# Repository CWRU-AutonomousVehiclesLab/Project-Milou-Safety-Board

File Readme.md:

# Project Milou Safety Board
This repo contains Project Milou's safety board design. The goal of this design is to have a standardized modular designed board that allow other competitor to improve their safety system.

## What is Project Milou?
Project Milou is Case Western Reserve University's second autonomous snowplow robot. The robot actively participate in the ION Autonomous Snowplow Challenge. Currently the latest revision of the robot is utilizing a Teensy 3.6, an ITX computer with a core i5 as its main control system.

## Logistics

**Latest revision is done at Febuary, 2020.**

The designer of this board can be traced back maybe 5 years, designed by folks working with Project Otto. This board re-layed out by Ziyi Huang as part of fullfilment for his senior project fall 2019. The board is modified by Frank (Chude Qian) to make it work on the robot. 

This project is maintained under CWRU Auontomous Vehicles Lab till 2021, and further maintained under CWRU Biologically Inspired Robotics (Biorobotics) Center. 

*Copyright belongs to CWRU Autonomous Vehicles lab, CWRU Biologically Inspired Robotics (Biorobotic) Center. Please use with acknowledgement.*

### Contact for questions
To contact email [Frank](mailto:cxq41@case.edu) if it is before 2021. If it is after 2021, email [Ian](mailto:ija2@case.edu) and [Dr. Merat](mailto:flm@case.edu). 

## How to use this?
To use the safety board design, you do not necessarily need to know about making PCBS. We recommend you to have some basic understanding of Egale the PCB software if you want to modify it. It should be fairly easy to use on a standardized ROS enabled robot.

### Pressumptions
The board assumes the following components: a 5V supply, a 12V supply, a standard RC Spread Specturum 2.4G remote reciever, a digital microcontroller that is capable of 5V or 3.3V digital input and output, a standard E-stop Button and a 12V relay.

### Materials
In order to use this PCB board, you will have to manufature it. We recommend [JLCPCB](https://jlcpcb.com/) which only cost about 10 USD for 5 boards. Unless you are mass manufacturing it, for sampling purposes, it should be good enough.

### Putting it together
In BOM folder, you will be able to find an excel sheet where it includes all of the materials you will need to put the board together. **NOTE: Do not use the value on the Eagle Schematics as they might by faulty. It is only used for manufacturing the PCB purpose.**

### 5V or 3.3V?
This board supports both 5V logic system and 3.3V logic system. If you need to have the logic output of the board to a 5V system, you should not solder R19 and R17 (aka a voltage divider to step down the 5V logic).

If your input voltage is normally 5V, I would recommend you use the Q4 component for Q5, instead of listed.

### Wiring it up!
Once you have completed all the steps above, you should be able to wire it up. To do so, start from left to right. The left side are all of the inputs.

**Supply**: The top of the supply terminal is +5V logic voltage, it is also used to power your Remote Reciever. A Ground is then followed. A 12V rail for driving the relay, and another ground.

**RCV-CH3**: For this 4 pin terminal, the top pin is your actual signal, and the middle one is 5V, and the bottom one is GND. Note that the last pin is not used, and additionally, the 5V pin can be disconnected if your RC reciever runs on a different voltage system. However, make sure that your GND is connected so that the system runs on the same reference.

**TEENSYIN** For this terminal, the top two are responsible for tracking the microcontroller output. This is designed allowing the microcontroller to throw an Estop exception and allowing the robot to be safely disabled from software. If your design do not have this feature, simply follow the 5V logic guideline and apply 5V directly on to the terminal. The bottom two are responsible for the Red ESTOP button. Simply wire the button to those two leads.

**TEENSYOUT** This is 4pin terminal on the right. This is all the output terminals. The top 2 terminals are wired directly to a relay to further drive a contactor for the robot. These two pin will run on 12V so make sure not to get it onto your microcontroller. The bottom two are signal for the microcontroller, allowing it to read the state of the ESTOP board. As always, top is signal, and bottom is GND. 

The board is designed to provide you ground wherever you might needed. For best practice you can also use twisted cable for delivering signal and reduce circuit noise interference.

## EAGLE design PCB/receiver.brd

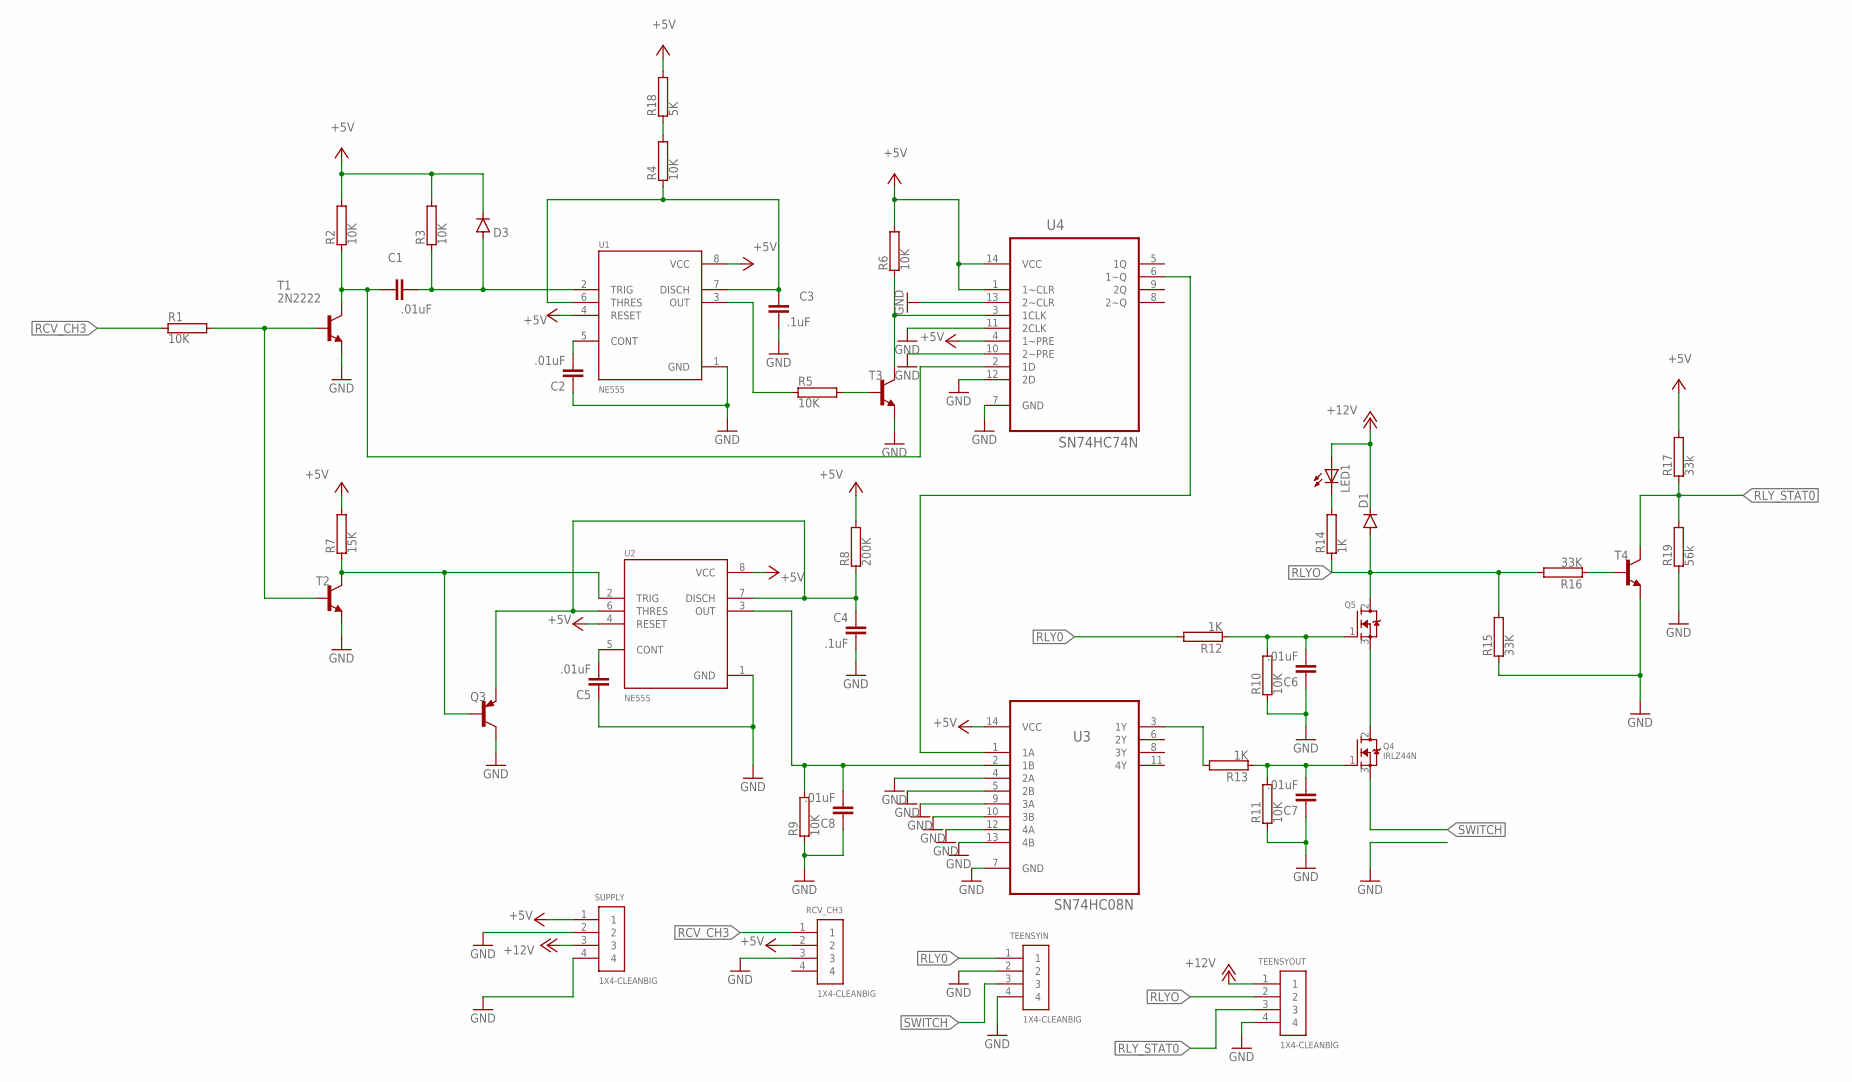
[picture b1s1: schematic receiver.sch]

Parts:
C1, C2, C5, C6, C7, C8: .01uF; C5B2.5
C3, C4: .1uF; C10B4
D1: 1N4004; DO41-10
D3: 1N4446; DO35-10
LED1: LED3MM
Q3: 2N2907; TO92-EBC-OVAL
Q4: IRLZ44N; TO220V
Q5: MOSFET-NGDS_TO220V; TO220V
R1, R2, R3, R4, R5, R6, R9, R10, R11: 10K; HPS58
R7: 15K; HPS58
R8: 200K; HPS58
R12, R13, R14: 1K; HPS58
R15, R16: 33K; HPS58
R17: 33k; HPS58
R18: 5K; HPS58
R19: 56k; HPS58
RCV_CH3: 1X4-CLEANBIG; 1X04-CLEANBIG
SUPPLY: 1X4-CLEANBIG; 1X04-CLEANBIG
T1, T2, T3, T4: 2N2222; TO92-EBC-OVAL
TEENSYIN: 1X4-CLEANBIG; 1X04-CLEANBIG
TEENSYOUT: 1X4-CLEANBIG; 1X04-CLEANBIG
U1, U2: NE555; DIP794W45P254L1060H508Q8
U3: SN74HC08N; DIP254P762X508-14
U4: SN74HC74N; DIP254P762X508-14

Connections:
+5V: D3.C, R2.2, R3.2, R6.2, R7.2, R8.2, R17.2, R18.2, RCV_CH3.2, SUPPLY.1, U1.4 (RESET), U1.8 (VCC), U2.4 (RESET), U2.8 (VCC), U3.14 (VCC), U4.1 (1~CLR), U4.4 (1~PRE), U4.14 (VCC)
+12V: D1.C, LED1.A, SUPPLY.3, TEENSYOUT.1
GND: C2.1, C3.2, C4.2, C5.1, C6.1, C7.1, C8.1, Q3.C, R9.1, R10.1, R11.1, R15.1, R19.1, RCV_CH3.3, SUPPLY.2, SUPPLY.4, T1.E, T2.E, T3.E, T4.E, TEENSYIN.2, TEENSYIN.4, TEENSYOUT.4, U1.1 (GND), U2.1 (GND), U3.4 (2A), U3.5 (2B), U3.7 (GND), U3.9 (3A), U3.10 (3B), U3.12 (4A), U3.13 (4B), U4.7 (GND), U4.10 (2~PRE), U4.11 (2CLK), U4.12 (2D), U4.13 (2~CLR)
unnamed: R1.2, T1.B, T2.B
unnamed: C1.2, R2.1, T1.C, U4.2 (1D)
unnamed: C1.1, D3.A, R3.1, U1.2 (TRIG)
unnamed: C2.2, U1.5 (CONT)
unnamed: C3.1, R4.1, U1.6 (THRES), U1.7 (DISCH)
unnamed: R5.1, U1.3 (OUT)
unnamed: R5.2, T3.B
unnamed: R6.1, T3.C, U4.3 (1CLK)
unnamed: Q3.B, R7.1, T2.C, U2.2 (TRIG)
unnamed: C4.1, Q3.E, R8.1, U2.6 (THRES), U2.7 (DISCH)
unnamed: C6.2, Q5.1 (G), R10.2, R12.1
unnamed: C8.2, R9.2, U2.3 (OUT), U3.2 (1B)
unnamed: C5.2, U2.5 (CONT)
unnamed: U3.1 (1A), U4.6 (1~Q)
unnamed: R4.2, R18.1
unnamed: C7.2, Q4.1 (G), R11.2, R13.1
unnamed: R13.2, U3.3 (1Y)
unnamed: LED1.K (C), R14.2
unnamed: Q4.2 (D), Q5.3 (S)
unnamed: R16.1, T4.B
RCV_CH3: R1.1, RCV_CH3.1
RLY0: R12.2, TEENSYIN.1
RLYO: D1.A, Q5.2 (D), R14.1, R15.2, R16.2, TEENSYOUT.2
RLY_STAT0: R17.1, R19.2, T4.C, TEENSYOUT.3
SWITCH: Q4.3 (S), TEENSYIN.3

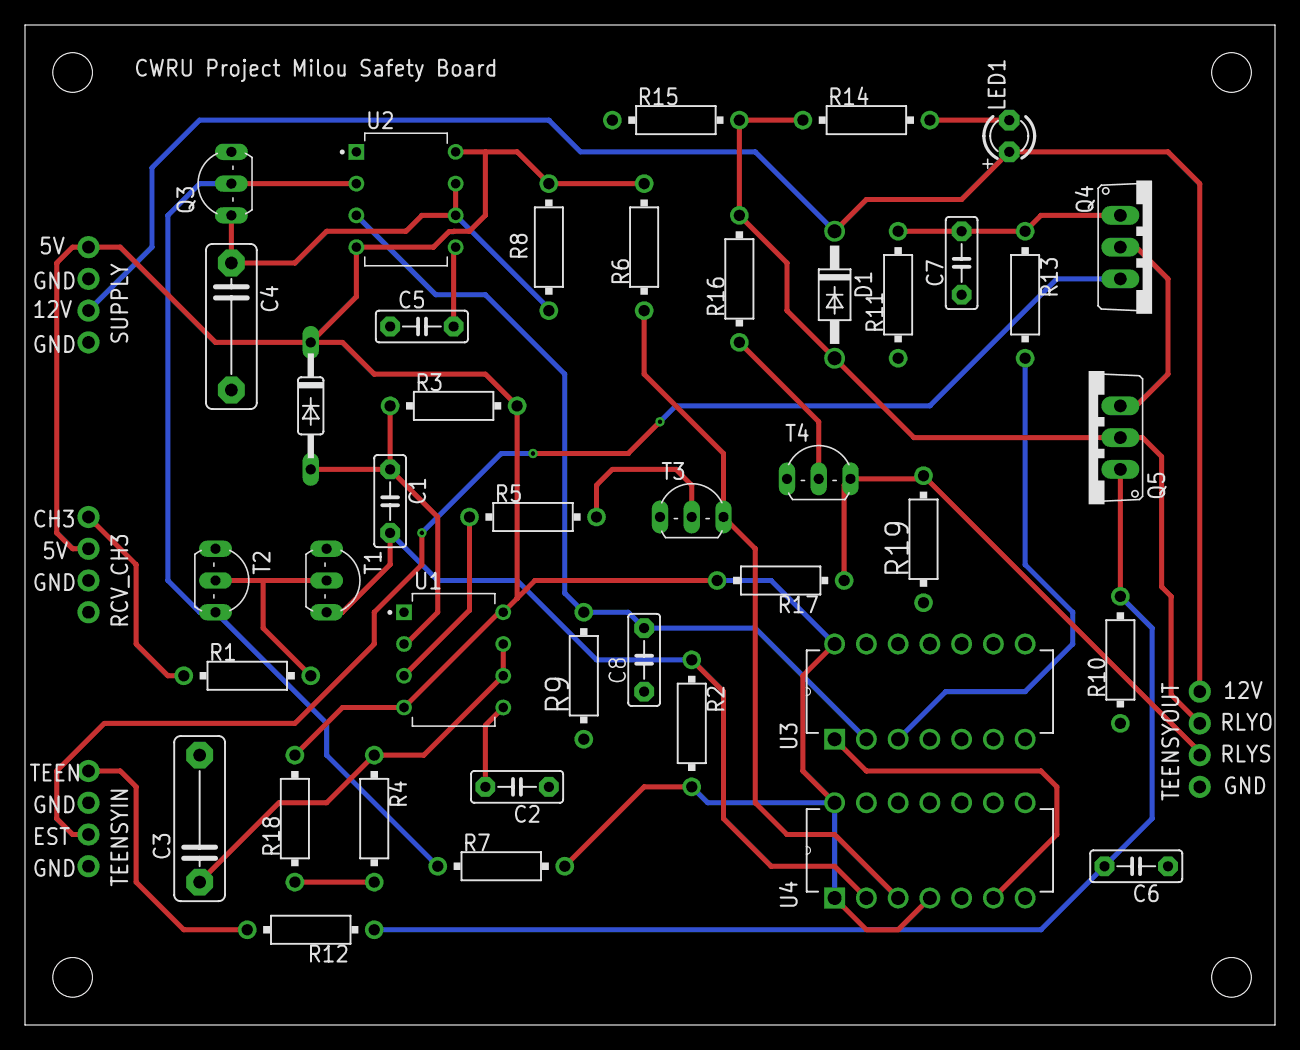
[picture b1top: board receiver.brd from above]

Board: 2 copper layers, 100.0 x 80.0 mm, 45 parts (0 on the bottom side), 28 nets.

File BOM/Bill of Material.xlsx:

Part | Value | Device | Package | Description | Multi Voltage OP Note
RCV_CH3 | 1X4-CLEANBIG | 1X4-CLEANBIG | 1X04-CLEANBIG | 4-pin connector
SUPPLY | 1X4-CLEANBIG | 1X4-CLEANBIG | 1X04-CLEANBIG | 4-pin connector
TEENSYIN | 1X4-CLEANBIG | 1X4-CLEANBIG | 1X04-CLEANBIG | 4-pin connector
TEENSYOUT | 1X4-CLEANBIG | 1X4-CLEANBIG | 1X04-CLEANBIG | 4-pin connector
C3 | .1uF | C10/4 | C10B4 | CAPACITOR
C4 | .1uF | C10/4 | C10B4 | CAPACITOR
C1 | .01uF | C5/2.5 | C5B2.5 | CAPACITOR
C2 | .01uF | C5/2.5 | C5B2.5 | CAPACITOR
C5 | .01uF | C5/2.5 | C5B2.5 | CAPACITOR
C6 | .01uF | C5/2.5 | C5B2.5 | CAPACITOR
C7 | .01uF | C5/2.5 | C5B2.5 | CAPACITOR
C8 | .01uF | C5/2.5 | C5B2.5 | CAPACITOR
U3 | SN74HC08N | SN74HC08N | DIP254P762X508-14 | QUADRUPLE 2-INPUT POSITIVE-NOR GATES
U4 | SN74HC74N | SN74HC74N | DIP254P762X508-14 | DUAL D-TYPE POSITIVE-EDGE-TRIGGERED FLIP-FLOPS
U1 | NE555 | NE555 | DIP794W45P254L1060H508Q8 | 555 timer
U2 | NE555 | NE555 | DIP794W45P254L1060H508Q8 | 555 timer
D3 | 1N4446 | 1N4446 | DO35-10 | DIODE
D1 | 1N4004 | 1N4004 | DO41-10 | DIODE
R1 | 10K | RHPS58 | HPS58 | Power Resitor
R10 | 10K | RHPS58 | HPS58 | Power Resitor
R11 | 10K | RHPS58 | HPS58 | Power Resitor
R12 | 1K | RHPS58 | HPS58 | Power Resitor
R13 | 1K | RHPS58 | HPS58 | Power Resitor
R14 | 1K | RHPS58 | HPS58 | Power Resitor
R15 | 33K | RHPS58 | HPS58 | Power Resitor
R16 | 33K | RHPS58 | HPS58 | Power Resitor
R17 | 33k | RHPS58 | HPS58 | Power Resitor | Optional, not needed for 5v output
R18 | 5.6K | RHPS58 | HPS58 | Power Resitor
R19 | 56k | RHPS58 | HPS58 | Power Resitor | Optional, not needed for 5v output
R2 | 10K | RHPS58 | HPS58 | Power Resitor
R3 | 10K | RHPS58 | HPS58 | Power Resitor
R4 | 10K | RHPS58 | HPS58 | Power Resitor
R5 | 10K | RHPS58 | HPS58 | Power Resitor
R6 | 10K | RHPS58 | HPS58 | Power Resitor
R7 | 15K | RHPS58 | HPS58 | Power Resitor
R8 | 200K | RHPS58 | HPS58 | Power Resitor
R9 | 10K | RHPS58 | HPS58 | Power Resitor
LED1 | RED | LED3MM | LED3MM | LED
Q4 | IRF530 | MOSFET-NGDS_TO220V | TO220V | N-Channel Mosfet
Q5 | IRLZ44N | MOSFET-NGDS_TO220V | TO220V | N-Channel Mosfet | Exchangable for 5V operation
Q3 | 2N4403 | 2N4403 | TO92-EBC-OVAL | PNP TRANSISTOR
T1 | 2N4401 | 2N4401 | TO92-EBC-OVAL | NPN TRANSISTOR
T2 | 2N4401 | 2N4401 | TO92-EBC-OVAL | NPN TRANSISTOR
T3 | 2N4401 | 2N4401 | TO92-EBC-OVAL | NPN TRANSISTOR
T4 | 2N4401 | 2N4401 | TO92-EBC-OVAL | NPN TRANSISTOR

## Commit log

2020-02-08 Completed Draft for Readme and uploaded files
2020-02-08 completed readme draft 1
2020-02-08 Added Lisence File
2020-02-08 added badges
2020-02-08 Set theme jekyll-theme-minimal

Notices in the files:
Readme.md:
MIT license
